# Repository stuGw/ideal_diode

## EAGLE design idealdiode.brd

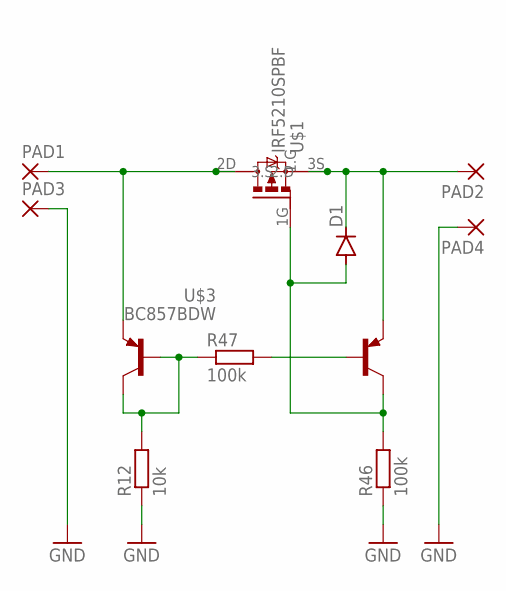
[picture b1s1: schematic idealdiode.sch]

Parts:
D1: DIODE-SMB; SMB
PAD1, PAD2, PAD3, PAD4: 2,54/1,0
R12: 10k; R0603
R46, R47: 100k; R0603
U$1: IRF5210SPBF; TO-220SMD
U$3: BC857BDW; SOT363-INFINION

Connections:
GND: PAD3.1, PAD4.1, R12.1, R46.1
unnamed: D1.A, R46.2, U$1.1G (1.G), U$3.3 (C)
unnamed: R12.2, R47.1, U$3.2 (B1), U$3.6 (C1)
unnamed: R47.2, U$3.5 (B)
unnamed: D1.C, PAD2.1, U$1.3S (3.S), U$3.4 (E)
unnamed: PAD1.1, U$1.2D (2.D), U$3.1 (E1)

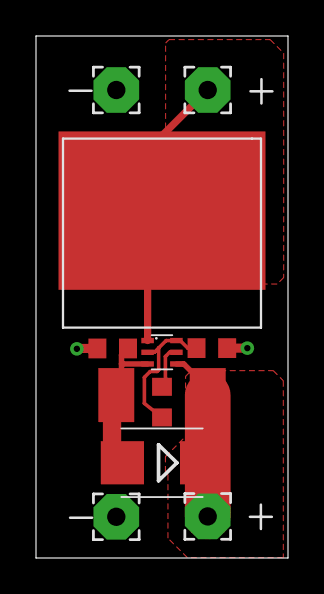
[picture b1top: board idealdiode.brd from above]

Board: 2 copper layers, 14.0 x 29.0 mm, 10 parts (0 on the bottom side), 6 nets.

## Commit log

2022-05-20 first
